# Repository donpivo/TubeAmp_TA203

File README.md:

Project description: https://retronics.no/tag/ta203/

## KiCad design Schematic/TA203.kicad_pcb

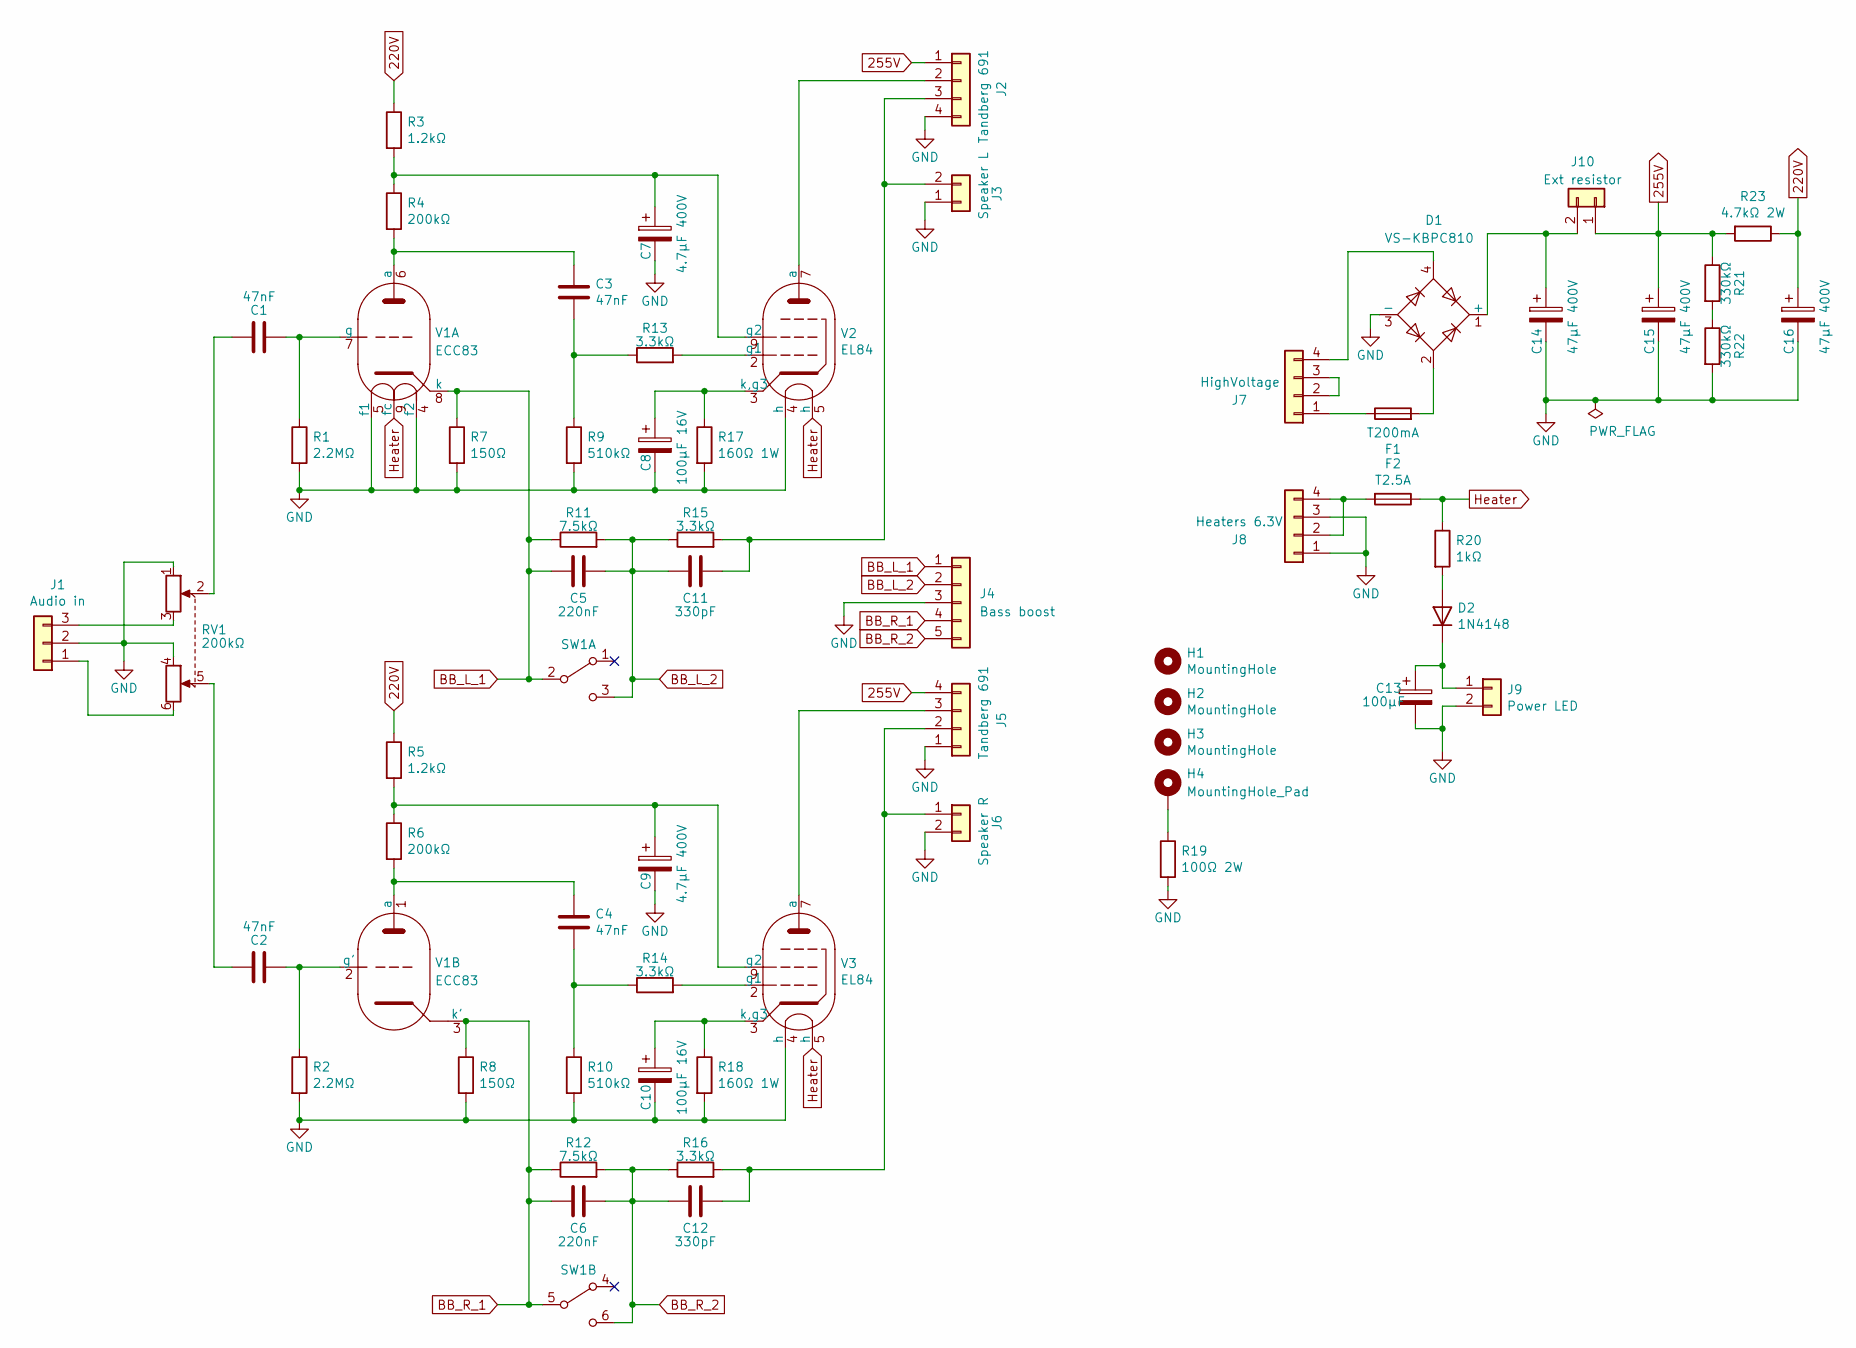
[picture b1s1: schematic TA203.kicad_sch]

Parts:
C1, C2, C3, C4: 47nF; C_Rect_L7.2mm_W7.2mm_P5.00mm_FKS2_FKP2_MKS2_MKP2
C5, C6: 220nF; C_Axial_L15.0mm_D7mm_P18.00mm_Horizontal
C7, C9: 4.7µF 400V; CP_Radial_D10.0mm_P5.00mm
C8, C10: 100µF 16V; CP_Radial_D5.0mm_P2.50mm
C11, C12: 330pF; C_Axial_L10.0mm_D6mm_P12.00mm_Horizontal
C13: 100µF; CP_Radial_D4.0mm_P2.00mm
C14, C15, C16: 47µF 400V; CP_Radial_D18.0mm_P7.50mm
D1: VS-KBPC810; Diode_Bridge_Vishay_KBPC810
D2: 1N4148; D_DO-35_SOD27_P7.62mm_Horizontal
F1: T200mA; Fuse_Littelfuse_372_D8.50mm
F2: T2.5A; Fuse_Littelfuse_372_D8.50mm
H1, H2, H3: MountingHole; MountingHole_3.2mm_M3
H4: MountingHole_Pad; MountingHole_3.2mm_M3_Pad_Via
J1: Audio in; KF2510-3P
J2, J5: Tandberg 691; TerminalBlock_LCSC_P5.08mm_4
J3: Speaker L; TerminalBlock_LCSC_P5.08mm
J4: Bass boost; KF2510-5P
J6: Speaker R; TerminalBlock_LCSC_P5.08mm
J7: HighVoltage; TerminalBlock_LCSC_P5.08mm_4
J8: Heaters 6.3V; TerminalBlock_LCSC_P5.08mm_4
J9: Power LED; PinHeader_1x02_P2.54mm_Vertical
J10: Ext resistor; TerminalBlock_LCSC_P5.08mm
R1, R2: 2.2MΩ; R_Axial_DIN0207_L6.3mm_D2.5mm_P7.62mm_Horizontal
R3, R5: 1.2kΩ; R_Axial_DIN0207_L6.3mm_D2.5mm_P7.62mm_Horizontal
R4, R6: 200kΩ; R_Axial_DIN0207_L6.3mm_D2.5mm_P7.62mm_Horizontal
R7, R8: 150Ω; R_Axial_DIN0207_L6.3mm_D2.5mm_P7.62mm_Horizontal
R9, R10: 510kΩ; R_Axial_DIN0207_L6.3mm_D2.5mm_P7.62mm_Horizontal
R11, R12: 7.5kΩ; R_Axial_DIN0207_L6.3mm_D2.5mm_P7.62mm_Horizontal
R13, R14, R15, R16: 3.3kΩ; R_Axial_DIN0207_L6.3mm_D2.5mm_P7.62mm_Horizontal
R17, R18: 160Ω 1W; R_Axial_DIN0414_L11.9mm_D4.5mm_P15.24mm_Horizontal
R19: 100Ω 2W; R_Axial_DIN0414_L11.9mm_D4.5mm_P15.24mm_Horizontal
R20: 1kΩ; R_Axial_DIN0207_L6.3mm_D2.5mm_P7.62mm_Horizontal
R21, R22: 330kΩ; R_Axial_DIN0207_L6.3mm_D2.5mm_P7.62mm_Horizontal
R23: 4.7kΩ 2W; R_Axial_DIN0414_L11.9mm_D4.5mm_P15.24mm_Horizontal
RV1: 200kΩ; Potentiometer_Alps_RK163_Dual_Horizontal
SW1: SW_DPDT_x2; JS202011CQN
V1: ECC83; Socket_Noval_Ceramic_1
V2, V3: EL84; Socket_Noval_Ceramic_1

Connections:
220V: C16.1, R3.1, R5.1, R23.1
255V: C15.1, J2.1, J5.4, J10.1, R21.1, R23.2
BB_L_1: C5.1, J4.1, R7.1, R11.1, SW1.2 (B), V1.8 (k)
BB_L_2: C5.2, C11.1, J4.2, R11.2, R15.1, SW1.3 (C)
BB_R_1: C6.1, J4.4, R8.1, R12.1, SW1.5 (B), V1.3 (k')
BB_R_2: C6.2, C12.1, J4.5, R12.2, R16.1, SW1.6 (C)
GND: C7.2, C8.2, C9.2, C10.2, C13.2, C14.2, C15.2, C16.2, D1.3 (-), J1.2, J2.4, J3.1, J4.3, J5.1, J6.2, J8.1, J8.3, J9.2, R1.2, R2.2, R7.2, R8.2, R9.2, R10.2, R17.2, R18.2, R19.2, R22.2, RV1.1, RV1.4, V1.4 (f2), V1.5 (f1), V2.4 (h), V3.4 (h)
Heater: F2.1, R20.1, V1.9 (fc), V2.5 (h), V3.5 (h)
unnamed: C1.1, R1.1, V1.7 (g)
unnamed: C1.2, RV1.2
unnamed: C2.1, R2.1, V1.2 (g')
unnamed: C2.2, RV1.5
unnamed: C3.1, R4.2, V1.6 (a)
unnamed: C3.2, R9.1, R13.1
unnamed: C4.1, R6.2, V1.1 (a)
unnamed: C4.2, R10.1, R14.1
unnamed: C7.1, R3.2, R4.1, V2.9 (g2)
unnamed: C8.1, R17.1, V2.3 (k,g3)
unnamed: C9.1, R5.2, R6.1, V3.9 (g2)
unnamed: C10.1, R18.1, V3.3 (k,g3)
unnamed: C11.2, J2.3, J3.2, R15.2
unnamed: C12.2, J5.2, J6.1, R16.2
unnamed: C13.1, D2.1 (K), J9.1
unnamed: C14.1, D1.1 (+), J10.2
unnamed: D1.2, F1.2
unnamed: D1.4, J7.4
unnamed: D2.2 (A), R20.2
unnamed: F1.1, J7.1
unnamed: F2.2, J8.2, J8.4
unnamed: H4.1, R19.1
unnamed: J1.1, RV1.6
unnamed: J1.3, RV1.3
unnamed: J2.2, V2.7 (a)
unnamed: J5.3, V3.7 (a)
unnamed: J7.2, J7.3
unnamed: R13.2, V2.2 (g1)
unnamed: R14.2, V3.2 (g1)
unnamed: R21.2, R22.1

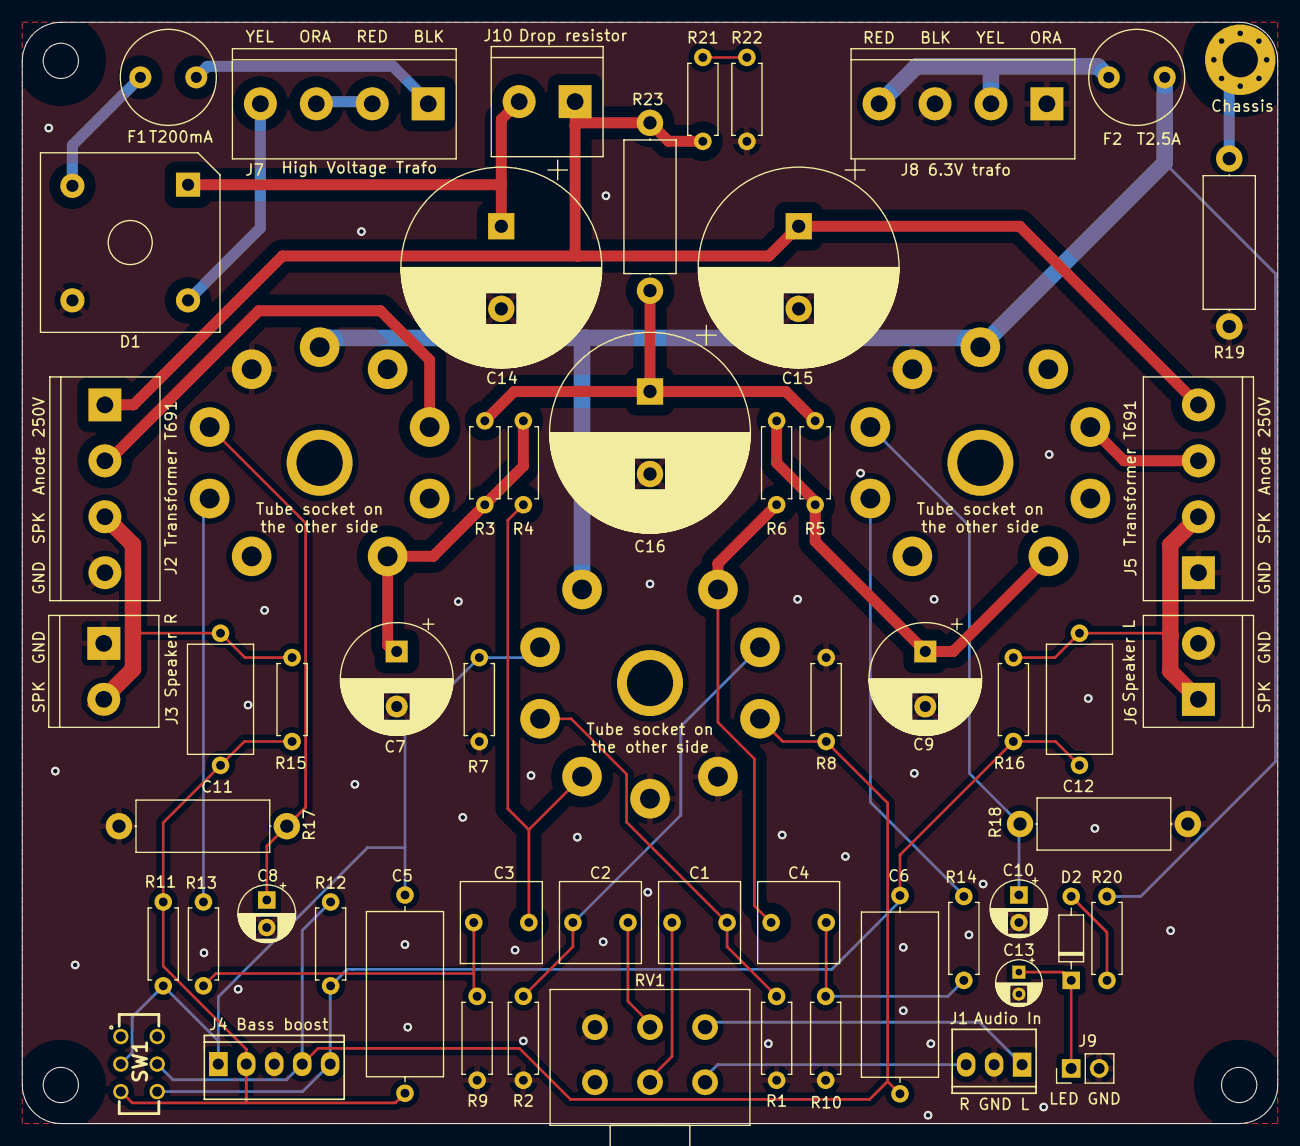
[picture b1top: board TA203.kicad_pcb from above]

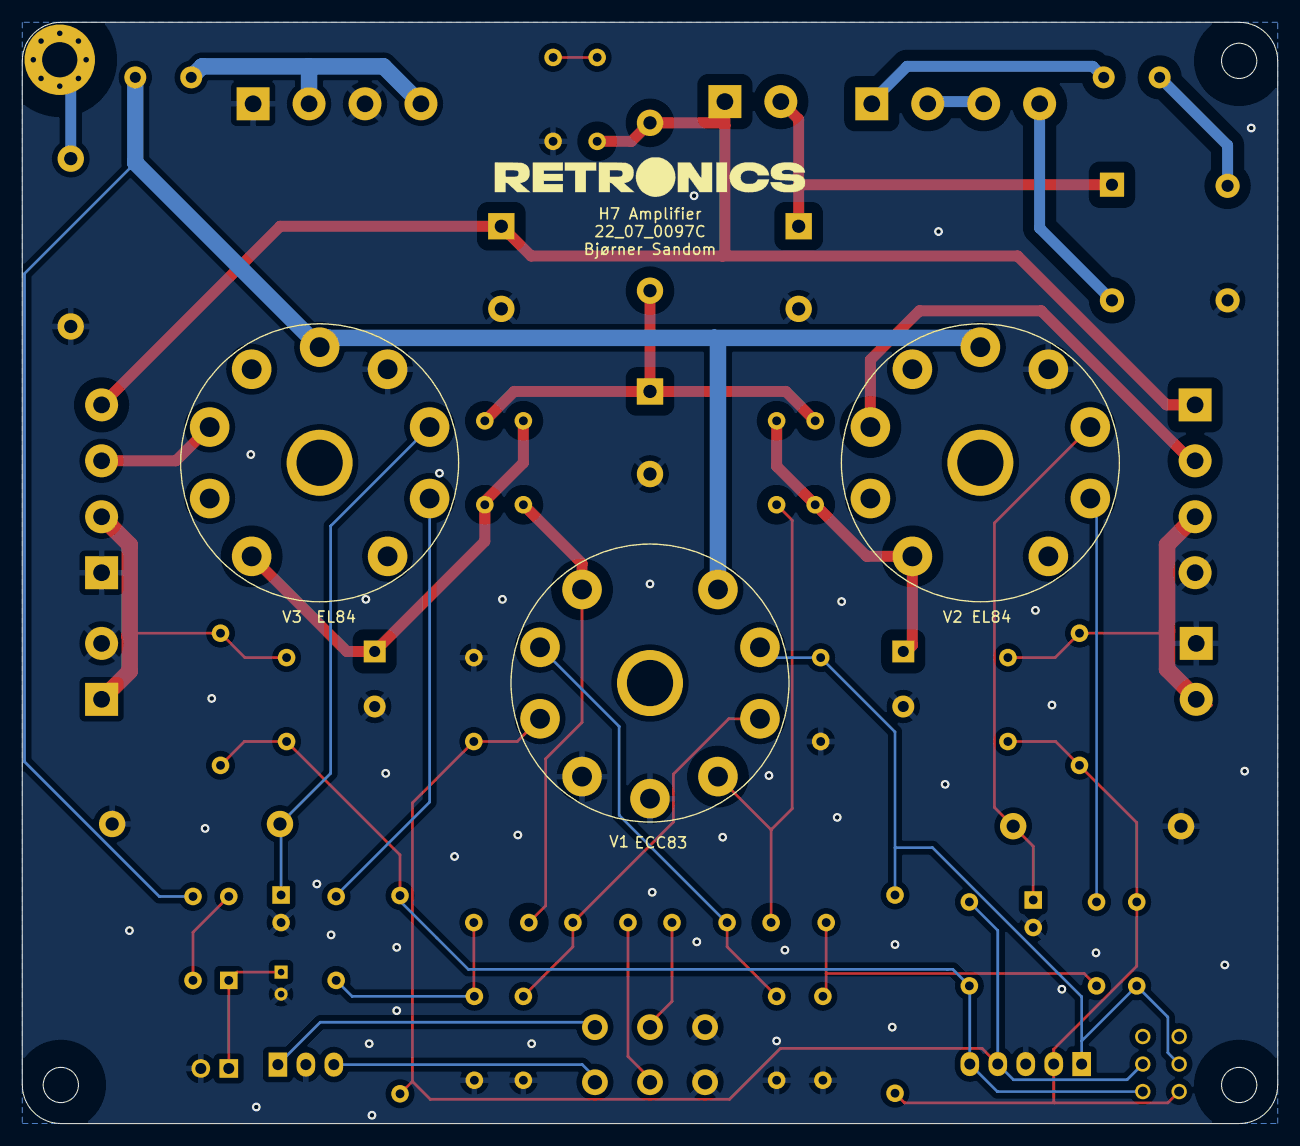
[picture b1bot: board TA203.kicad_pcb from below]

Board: 2 copper layers, 114.0 x 100.0 mm, 62 parts (3 on the bottom side), 38 nets.

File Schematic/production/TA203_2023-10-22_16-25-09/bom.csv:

Designator,Footprint,Quantity,Value,LCSC Part #
"C1, C2, C3, C4",C_Rect_L7.2mm_W7.2mm_P5.00mm_FKS2_FKP2_MKS2_MKP2,4,47nF,
"C10, C8",CP_Radial_D5.0mm_P2.50mm,2,100µF 16V,
"C11, C12",C_Axial_L10.0mm_D6mm_P12.00mm_Horizontal,2,330pF,
C13,CP_Radial_D4.0mm_P2.00mm,1,22µF,
"C14, C15, C16",CP_Radial_D18.0mm_P7.50mm,3,47µF 400V,
"C5, C6",C_Axial_L15.0mm_D7mm_P18.00mm_Horizontal,2,220nF,
"C7, C9",CP_Radial_D10.0mm_P5.00mm,2,4.7µF 400V,
D1,Diode_Bridge_Vishay_KBPC810,1,VS-KBPC810,
D2,D_DO-35_SOD27_P7.62mm_Horizontal,1,1N4148,
F1,Fuse_Littelfuse_372_D8.50mm,1,T200mA,
F2,Fuse_Littelfuse_372_D8.50mm,1,T2.5A,
"H1, H2, H3",MountingHole_3.2mm_M3,3,MountingHole,
H4,MountingHole_3.2mm_M3_Pad_Via,1,MountingHole_Pad,
J1,KF2510-3P,1,Audio in,
J10,TerminalBlock_LCSC_P5.08mm,1,Ext resistor,
"J2, J5",TerminalBlock_LCSC_P5.08mm_4,2,Tandberg 691,
J3,TerminalBlock_LCSC_P5.08mm,1,Speaker L,
J4,KF2510-5P,1,Bass boost,
J6,TerminalBlock_LCSC_P5.08mm,1,Speaker R,
J7,TerminalBlock_LCSC_P5.08mm_4,1,HighVoltage,
J8,TerminalBlock_LCSC_P5.08mm_4,1,Heaters 6.3V,
J9,PinHeader_1x02_P2.54mm_Vertical,1,Power LED,
"R1, R2",R_Axial_DIN0207_L6.3mm_D2.5mm_P7.62mm_Horizontal,2,10MΩ,
"R10, R9",R_Axial_DIN0207_L6.3mm_D2.5mm_P7.62mm_Horizontal,2,510kΩ,
"R11, R12",R_Axial_DIN0207_L6.3mm_D2.5mm_P7.62mm_Horizontal,2,7.5kΩ,
"R13, R14, R15, R16",R_Axial_DIN0207_L6.3mm_D2.5mm_P7.62mm_Horizontal,4,3.3kΩ,
"R17, R18",R_Axial_DIN0414_L11.9mm_D4.5mm_P15.24mm_Horizontal,2,160Ω 1W,
R19,R_Axial_DIN0414_L11.9mm_D4.5mm_P15.24mm_Horizontal,1,100Ω 2W,
R20,R_Axial_DIN0207_L6.3mm_D2.5mm_P7.62mm_Horizontal,1,330Ω,
"R21, R22",R_Axial_DIN0207_L6.3mm_D2.5mm_P7.62mm_Horizontal,2,330kΩ,
R23,R_Axial_DIN0414_L11.9mm_D4.5mm_P15.24mm_Horizontal,1,8.2kΩ 2W,
"R3, R5",R_Axial_DIN0207_L6.3mm_D2.5mm_P7.62mm_Horizontal,2,1.2kΩ,
"R4, R6",R_Axial_DIN0207_L6.3mm_D2.5mm_P7.62mm_Horizontal,2,200kΩ,
"R7, R8",R_Axial_DIN0207_L6.3mm_D2.5mm_P7.62mm_Horizontal,2,150Ω,
RV1,Potentiometer_Alps_RK163_Dual_Horizontal,1,200kΩ,
SW1,JS202011CQN,1,SW_DPDT_x2,
V1,Socket_Noval_Ceramic_1,1,ECC83,
"V2, V3",Socket_Noval_Ceramic_1,2,EL84,

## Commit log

2023-10-22 Updated production files
